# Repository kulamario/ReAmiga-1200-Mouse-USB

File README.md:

ReAmiga USB Mouse Adapter 

Project was created in cooperation with Arkadiusz Makarenko
I created the PCB and Arek Makarenko made the software

STM32F401RBT6TR was used
Software can be uploaded using STM32CUBE
Board has two LEDs 
One for Power and the other for connection to a USB device
The adapter working great with HID mouse

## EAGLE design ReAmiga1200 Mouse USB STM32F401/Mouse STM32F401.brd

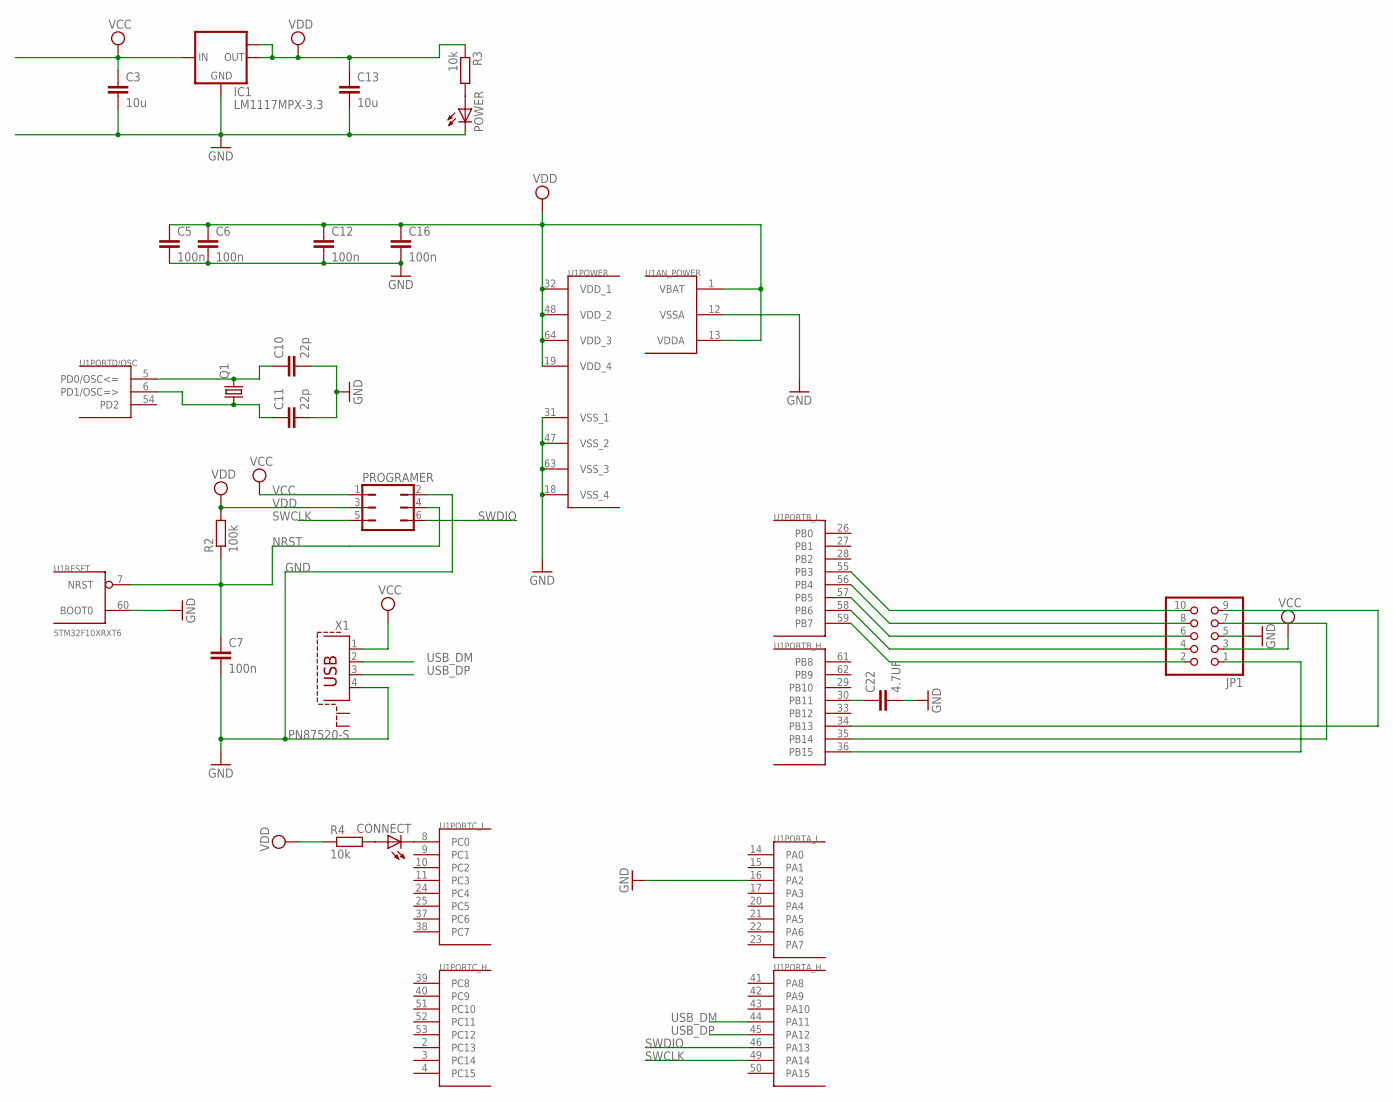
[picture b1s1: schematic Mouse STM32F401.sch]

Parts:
C3, C13: 10u; C1206
C5, C6, C7, C12, C16: 100n; C0603
C10, C11: 22p; C0603
C22: 4.7UF; C1206
CONNECT: LEDSML0805; SML0805
IC1: LM1117MPX-3.3; SOT223
JP1: PINHD-2X5; 2X05
POWER: LEDSML0805; SML0805
PROGRAMER: JP3Q
Q1: CRYSTALHC49S; HC49/S
R2: 100k; R0603
R3, R4: 10k; R0603
U1: STM32F10XRXT6; TQFP64
X1: PN87520-S

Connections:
GND: C3.2, C5.2, C6.2, C7.2, C10.2, C11.2, C12.2, C13.2, C16.2, C22.2, IC1.1 (GND), JP1.5, POWER.C, PROGRAMER.2, U1.12 (VSSA), U1.16 (PA2), U1.18 (VSS_4), U1.31 (VSS_1), U1.47 (VSS_2), U1.60 (BOOT0), U1.63 (VSS_3), X1.4
unnamed: C10.1, Q1.2, U1.5 (PD0/OSC<=)
unnamed: C11.1, Q1.1, U1.6 (PD1/OSC=>)
unnamed: CONNECT.C, U1.8 (PC0)
unnamed: C22.1, U1.30 (PB11)
unnamed: JP1.10, U1.55 (PB3)
unnamed: CONNECT.A, R4.2
unnamed: JP1.8, U1.56 (PB4)
unnamed: JP1.6, U1.57 (PB5)
unnamed: JP1.4, U1.58 (PB6)
unnamed: JP1.2, U1.59 (PB7)
unnamed: POWER.A, R3.2
unnamed: JP1.7, U1.35 (PB14)
unnamed: JP1.9, U1.34 (PB13)
unnamed: JP1.1, U1.36 (PB15)
NRST: C7.1, PROGRAMER.4, R2.1, U1.7 (NRST)
SWCLK: PROGRAMER.5, U1.49 (PA14)
SWDIO: PROGRAMER.6, U1.46 (PA13)
USB_DM: U1.44 (PA11), X1.2
USB_DP: U1.45 (PA12), X1.3
VCC: C3.1, IC1.3 (IN), JP1.3, PROGRAMER.1, X1.1
VDD: C5.1, C6.1, C12.1, C13.1, C16.1, IC1.2 (OUT), IC1.TAB (OUT1), PROGRAMER.3, R2.2, R3.1, R4.1, U1.1 (VBAT), U1.13 (VDDA), U1.19 (VDD_4), U1.32 (VDD_1), U1.48 (VDD_2), U1.64 (VDD_3)

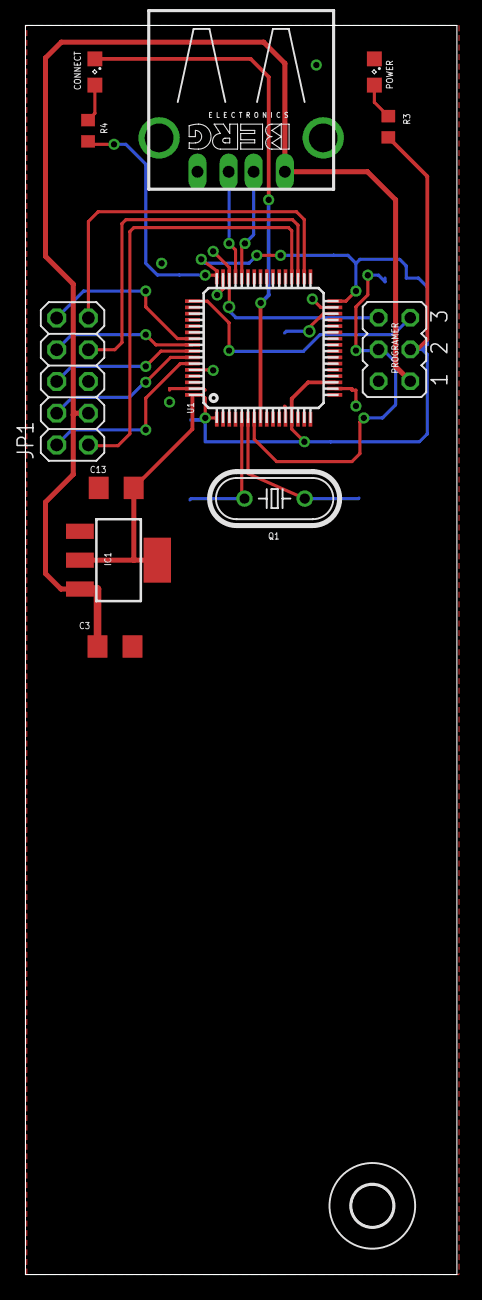
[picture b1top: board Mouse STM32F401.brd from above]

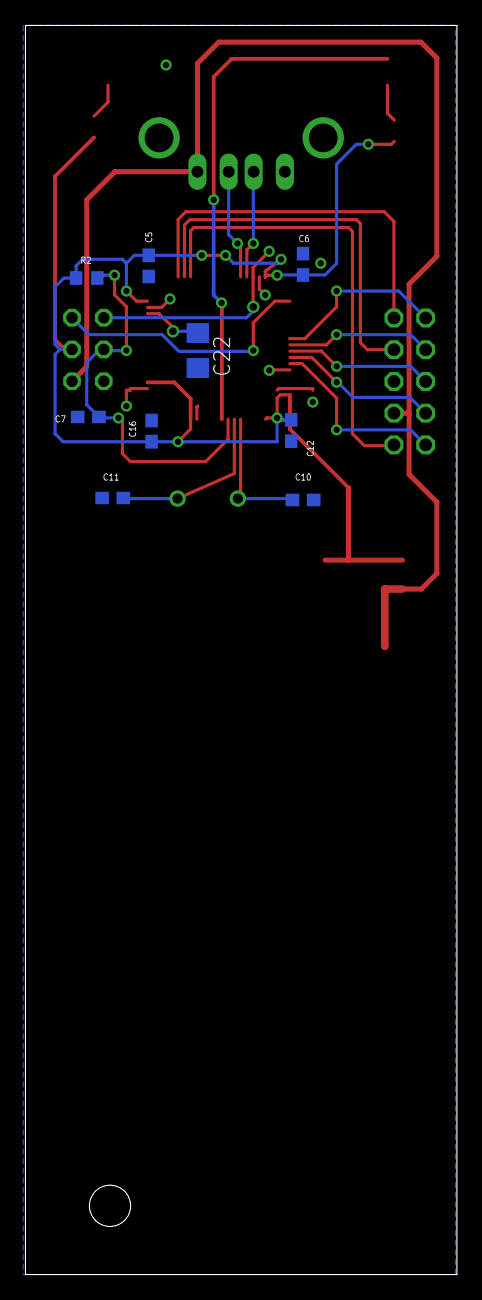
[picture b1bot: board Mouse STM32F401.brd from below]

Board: 2 copper layers, 34.5 x 100.0 mm, 22 parts (9 on the bottom side), 22 nets.

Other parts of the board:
U$1: 3,3

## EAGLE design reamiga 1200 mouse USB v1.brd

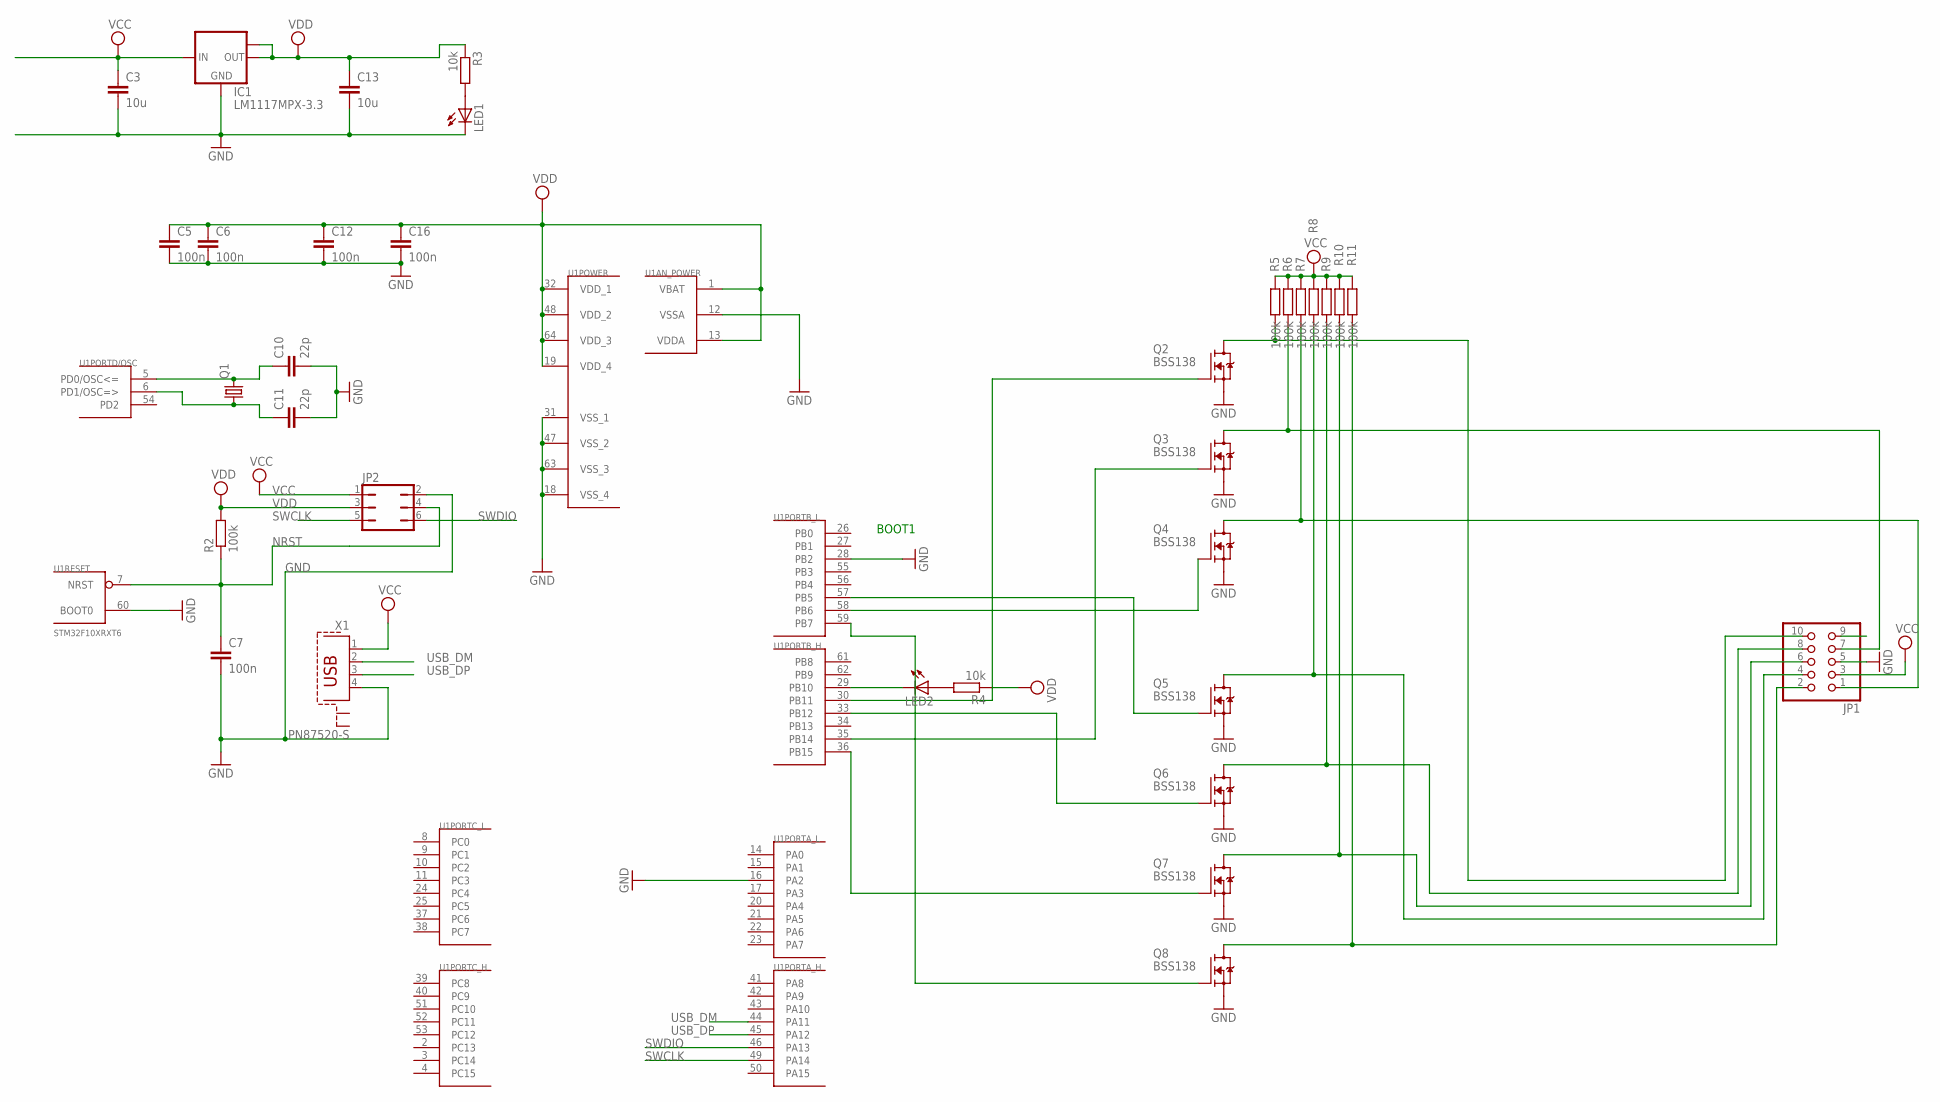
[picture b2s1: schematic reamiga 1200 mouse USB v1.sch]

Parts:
C3, C13: 10u; C1206
C5, C6, C7, C12, C16: 100n; C0603
C10, C11: 22p; C0603
IC1: LM1117MPX-3.3; SOT223
JP1: PINHD-2X5; 2X05
JP2: JP3Q
LED1, LED2: LEDSML0805; SML0805
Q1: CRYSTALHC49S; HC49/S
Q2, Q3, Q4, Q5, Q6, Q7, Q8: BSS138; SOT23
R2, R5, R6, R7, R8, R9, R10, R11: 100k; R0603
R3, R4: 10k; R0603
U1: STM32F10XRXT6; TQFP64
X1: PN87520-S

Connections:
GND: C3.2, C5.2, C6.2, C7.2, C10.2, C11.2, C12.2, C13.2, C16.2, IC1.1 (GND), JP1.5, JP2.2, LED1.C, Q2.2 (S), Q3.2 (S), Q4.2 (S), Q5.2 (S), Q6.2 (S), Q7.2 (S), Q8.2 (S), U1.12 (VSSA), U1.16 (PA2), U1.18 (VSS_4), U1.28 (PB2), U1.31 (VSS_1), U1.47 (VSS_2), U1.60 (BOOT0), U1.63 (VSS_3), X1.4
unnamed: C10.1, Q1.2, U1.5 (PD0/OSC<=)
unnamed: C11.1, Q1.1, U1.6 (PD1/OSC=>)
unnamed: Q3.1 (G), U1.35 (PB14)
unnamed: Q5.1 (G), U1.57 (PB5)
unnamed: Q4.1 (G), U1.58 (PB6)
unnamed: LED2.A, R4.2
unnamed: LED2.C, U1.29 (PB10)
unnamed: LED1.A, R3.2
unnamed: Q2.1 (G), U1.30 (PB11)
unnamed: Q6.1 (G), U1.33 (PB12)
unnamed: Q7.1 (G), U1.36 (PB15)
unnamed: Q8.1 (G), U1.59 (PB7)
unnamed: JP1.10, Q2.3 (D), R5.2
unnamed: JP1.7, Q3.3 (D), R6.2
unnamed: JP1.1, Q4.3 (D), R7.2
unnamed: JP1.4, Q5.3 (D), R8.2
unnamed: JP1.8, Q6.3 (D), R9.2
unnamed: JP1.6, Q7.3 (D), R10.2
unnamed: JP1.2, Q8.3 (D), R11.2
NRST: C7.1, JP2.4, R2.1, U1.7 (NRST)
SWCLK: JP2.5, U1.49 (PA14)
SWDIO: JP2.6, U1.46 (PA13)
USB_DM: U1.44 (PA11), X1.2
USB_DP: U1.45 (PA12), X1.3
VCC: C3.1, IC1.3 (IN), JP1.3, JP2.1, R5.1, R6.1, R7.1, R8.1, R9.1, R10.1, R11.1, X1.1
VDD: C5.1, C6.1, C12.1, C13.1, C16.1, IC1.2 (OUT), IC1.TAB (OUT1), JP2.3, R2.2, R3.1, R4.1, U1.1 (VBAT), U1.13 (VDDA), U1.19 (VDD_4), U1.32 (VDD_1), U1.48 (VDD_2), U1.64 (VDD_3)

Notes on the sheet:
BOOT1

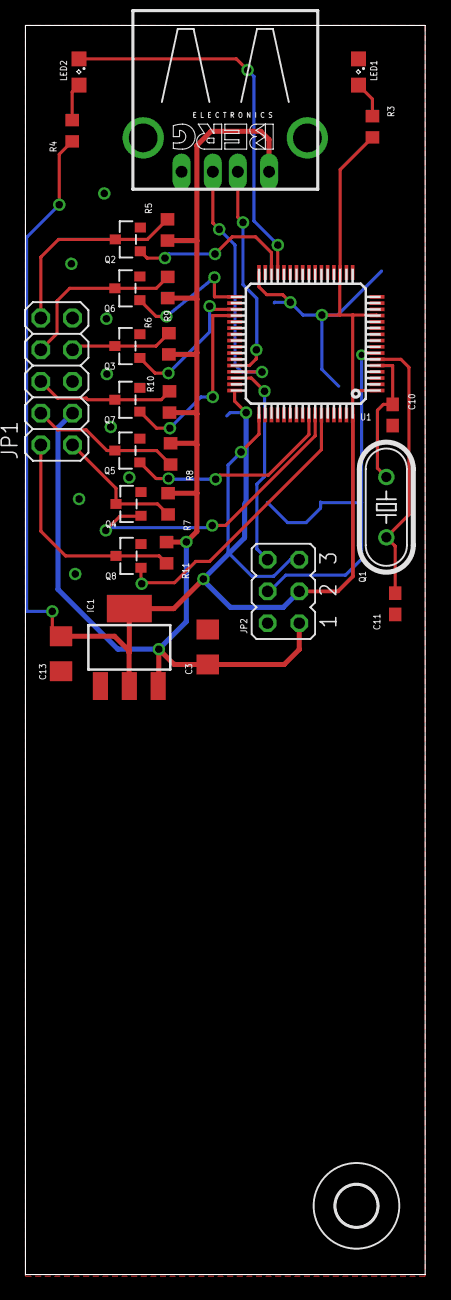
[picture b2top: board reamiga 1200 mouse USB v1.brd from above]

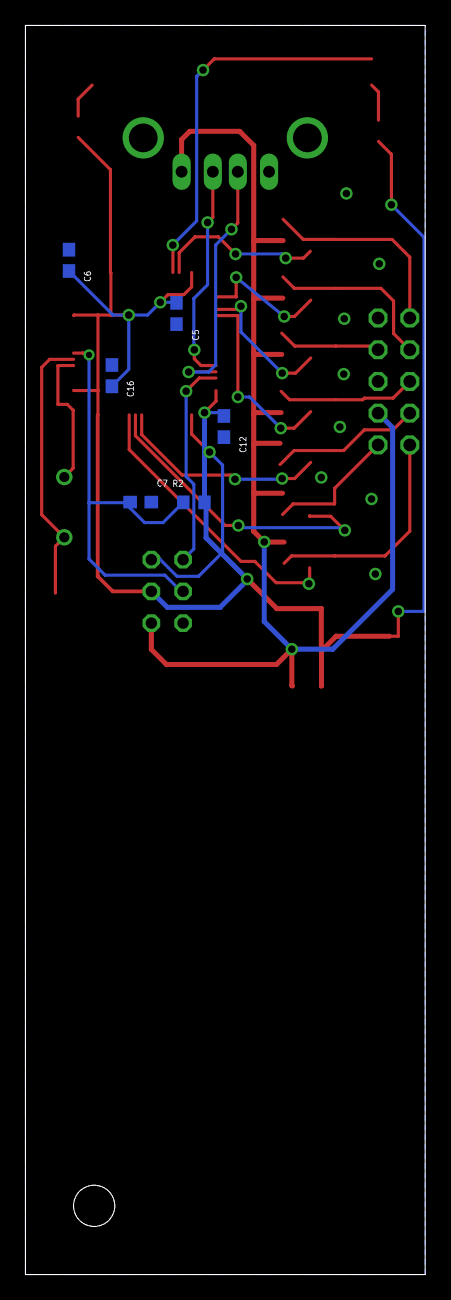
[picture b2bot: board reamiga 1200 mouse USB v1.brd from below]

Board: 2 copper layers, 32.0 x 100.0 mm, 35 parts (6 on the bottom side), 27 nets.

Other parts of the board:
U$1: 3,3
